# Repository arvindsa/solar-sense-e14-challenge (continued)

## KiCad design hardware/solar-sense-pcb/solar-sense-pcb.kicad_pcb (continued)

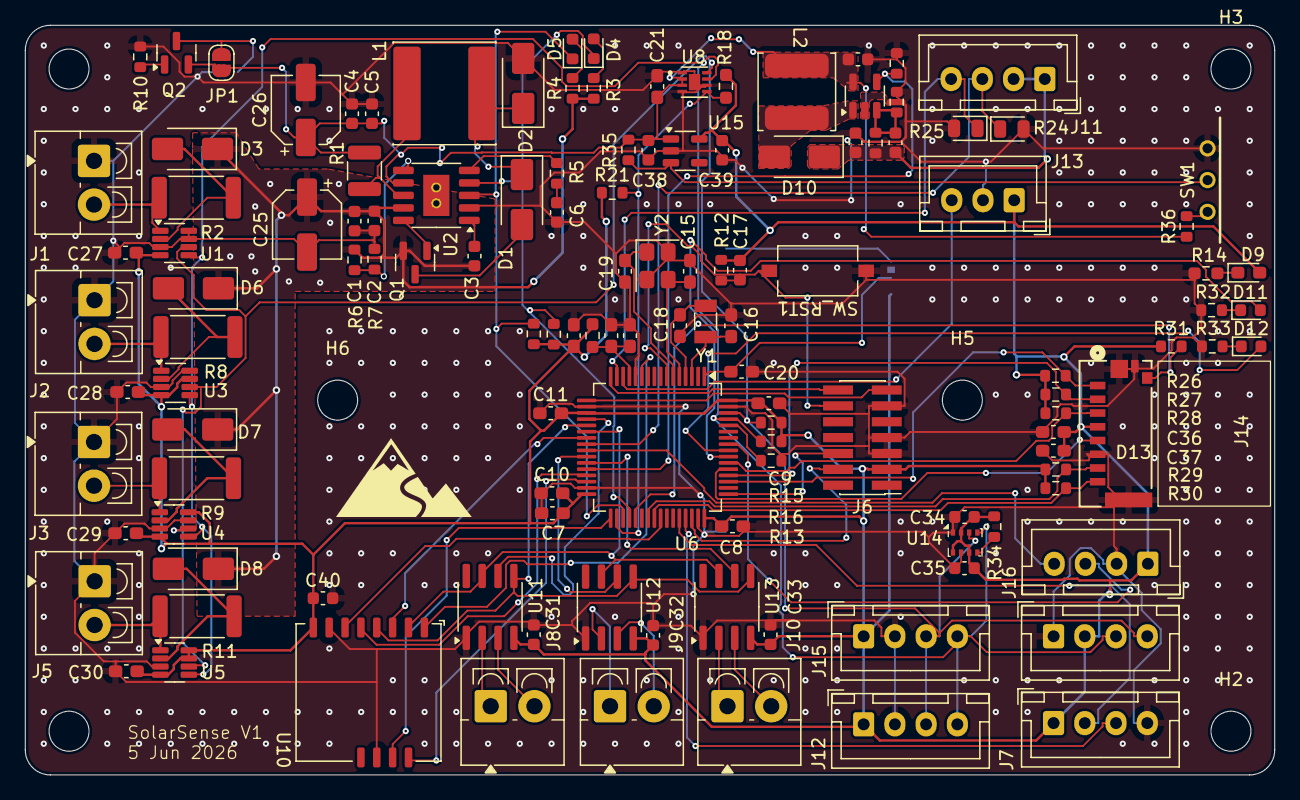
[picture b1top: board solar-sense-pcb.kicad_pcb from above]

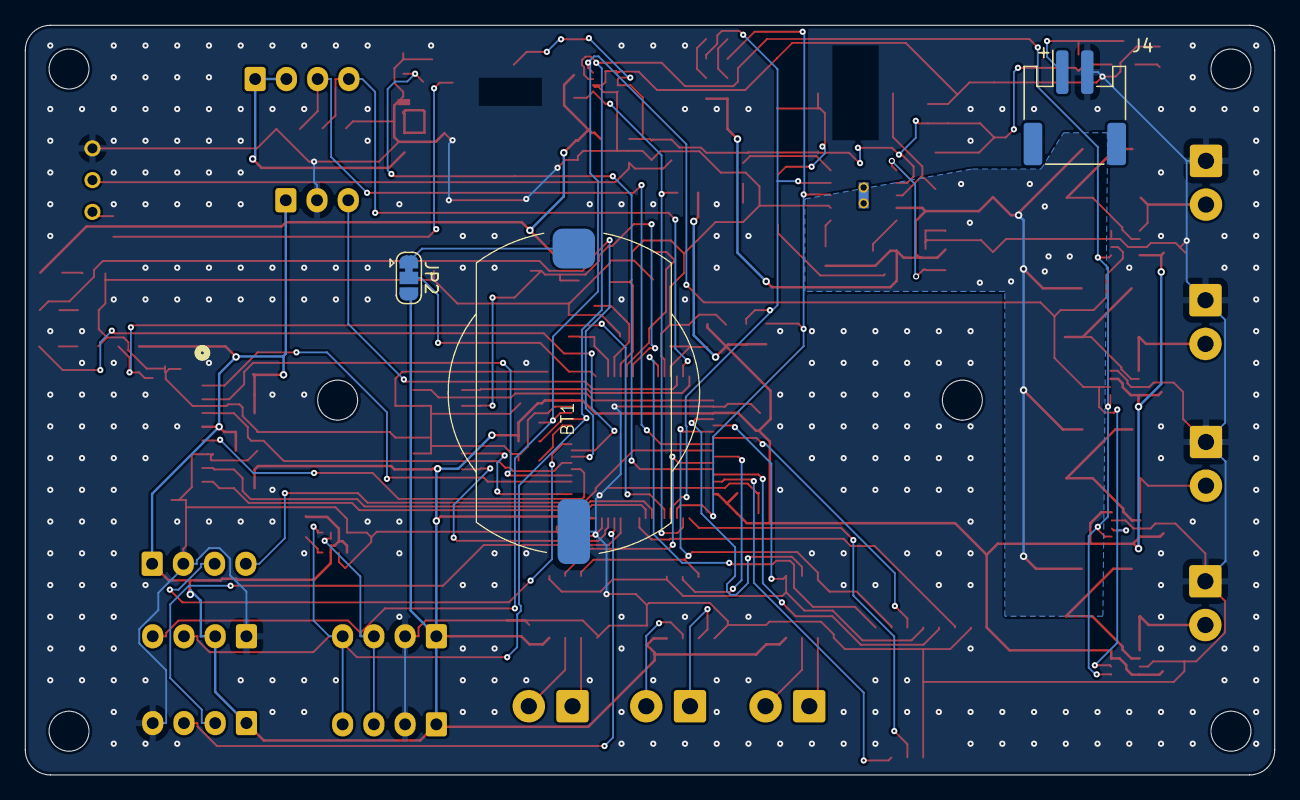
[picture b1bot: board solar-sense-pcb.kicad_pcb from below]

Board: 2 copper layers, 100.0 x 60.0 mm, 138 parts (3 on the bottom side), 86 nets.

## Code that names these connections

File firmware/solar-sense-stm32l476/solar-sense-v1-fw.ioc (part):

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Mcu.Name=STM32L476R(C-E-G)Tx
Mcu.Package=LQFP64
Mcu.UserName=STM32L476RGTx
PA0.GPIOParameters=GPIO_Label
PA0.GPIO_Label=ADC_UV
PA0.Signal=ADCx_IN5
PA1.GPIOParameters=GPIO_Label
PA1.GPIO_Label=ADC_HX94C_RH
PA1.Signal=ADCx_IN6
PA11.Mode=CAN_Activate
PA11.Signal=CAN1_RX
PA12.Mode=CAN_Activate
PA12.Signal=CAN1_TX
PA13\ (JTMS-SWDIO).Mode=Serial_Wire
PA13\ (JTMS-SWDIO).Signal=SYS_JTMS-SWDIO
PA14\ (JTCK-SWCLK).Mode=Serial_Wire
PA14\ (JTCK-SWCLK).Signal=SYS_JTCK-SWCLK
PA2.Mode=Asynchronous
PA2.Signal=USART2_TX
PA3.Mode=Asynchronous
PA3.Signal=USART2_RX
PA4.GPIOParameters=PinState,GPIO_Label
PA4.GPIO_Label=TC1_CS
PA4.PinState=GPIO_PIN_SET
PA4.Signal=GPIO_Output
PA5.Mode=Full_Duplex_Master
PA5.Signal=SPI1_SCK
PA6.Mode=Full_Duplex_Master
PA6.Signal=SPI1_MISO
PA7.Mode=Full_Duplex_Master
PA7.Signal=SPI1_MOSI
PA8.GPIOParameters=PinState,GPIO_Label
PA8.GPIO_Label=LORA_CS
PA8.PinState=GPIO_PIN_SET
PA8.Signal=GPIO_Output
PB0.GPIOParameters=PinState,GPIO_Label
PB0.GPIO_Label=TC2_CS
PB0.PinState=GPIO_PIN_SET
PB0.Signal=GPIO_Output
PB1.GPIOParameters=PinState,GPIO_Label
PB1.GPIO_Label=TC3_CS
PB1.PinState=GPIO_PIN_SET
PB1.Signal=GPIO_Output
PB10.GPIOParameters=GPIO_Label
PB10.GPIO_Label=LORA_RESET
PB10.Signal=GPIO_Output
PB11.GPIOParameters=GPIO_Label
PB11.GPIO_Label=LORA_DIO1
PB11.Signal=GPIO_Input
PB12.GPIOParameters=GPIO_Label
PB12.GPIO_Label=LORA_BUSY
PB12.Signal=GPIO_Input
PB13.GPIOParameters=GPIO_Label
PB13.GPIO_Label=BAT_ALRT
PB13.Signal=GPIO_Input
PB14.GPIOParameters=GPIO_Label
PB14.GPIO_Label=CN3791_CHRG
PB14.Signal=GPIO_Input
PB15.GPIOParameters=GPIO_Label
PB15.GPIO_Label=CN3791_DONE
PB15.Signal=GPIO_Input
PB2.GPIOParameters=GPIO_Label
PB2.GPIO_Label=EN_12V
PB2.Signal=GPIO_Output
PB3\ (JTDO-TRACESWO).GPIOParameters=GPIO_Label
PB3\ (JTDO-TRACESWO).GPIO_Label=LED_STATUS
PB3\ (JTDO-TRACESWO).Signal=GPIO_Output
PB4\ (NJTRST).GPIOParameters=GPIO_Label
PB4\ (NJTRST).GPIO_Label=LED_ERR
PB4\ (NJTRST).Signal=GPIO_Output
PB5.GPIOParameters=GPIO_Label
PB5.GPIO_Label=RAIN_DET
PB5.Signal=GPIO_Input
PB8.Mode=I2C
PB8.Signal=I2C1_SCL
PB9.Mode=I2C
PB9.Signal=I2C1_SDA
PC10.Mode=SD_4_bits_Wide_bus
PC10.Signal=SDMMC1_D2
PC11.Mode=SD_4_bits_Wide_bus
PC11.Signal=SDMMC1_D3
PC12.Mode=SD_4_bits_Wide_bus
PC12.Signal=SDMMC1_CK
PC14-OSC32_IN\ (PC14).Mode=LSE-External-Oscillator
PC14-OSC32_IN\ (PC14).Signal=RCC_OSC32_IN
PC15-OSC32_OUT\ (PC15).Mode=LSE-External-Oscillator
PC15-OSC32_OUT\ (PC15).Signal=RCC_OSC32_OUT
PC3.Signal=GPIO_Output
PC4.GPIOParameters=GPIO_Label
PC4.GPIO_Label=ADC_HX94C_TEMP
PC4.Signal=ADCx_IN13
PC5.GPIOParameters=GPIO_Label
PC5.GPIO_Label=RAIN_AO
PC5.Signal=ADCx_IN14
PC6.GPIOParameters=GPIO_Label
PC6.GPIO_Label=SDMMC1_CD
PC6.Signal=GPIO_Input
PC8.Mode=SD_4_bits_Wide_bus
PC8.Signal=SDMMC1_D0
PC9.Mode=SD_4_bits_Wide_bus
PC9.Signal=SDMMC1_D1
PD2.Mode=SD_4_bits_Wide_bus
PD2.Signal=SDMMC1_CMD
PH0-OSC_IN\ (PH0).Mode=HSE-External-Oscillator
PH0-OSC_IN\ (PH0).Signal=RCC_OSC_IN
PH1-OSC_OUT\ (PH1).Mode=HSE-External-Oscillator
PH1-OSC_OUT\ (PH1).Signal=RCC_OSC_OUT
RCC.HSE_VALUE=8000000
RCC.SYSCLKFreq_VALUE=80000000
RCC.SYSCLKSource=RCC_SYSCLKSOURCE_PLLCLK
board=custom

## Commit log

2026-06-21 Added disclaimer
2026-06-21 Added e14 project link
2026-06-21 Added clarity on Labview test python file
